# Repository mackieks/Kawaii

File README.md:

<picture> <source media="(prefers-color-scheme: dark)" srcset="images/kawaii_logo_white.png">  </picture> 

Kawaii is a functional metal Nintendo Wii keychain created by YveltalGriffin, Wesk and Ding.

It's a technical tour de force that prioritizes aesthetics over practicality, and **fully** utilizes the OMEGA trim.

Kawaii may be the zenith of Wii portablizing as an artform.

## Features:
- [x] 60 x 60 x 15.8mm CNC aluminum chassis
- [x] Anodized, with laser-etched artwork
- [x] Fake compliance markings
- [x] Keychain / tassel loop
- [x] OMEGA-trimmed undervolted Hollywood-2 Wii Mini motherboard
- [x] [AVEflex](https://github.com/mackieks/AVEflex) and [nandFlex](https://github.com/mackieks/nandFlex)
- [x] Powered by [Thundervolt](https://github.com/mackieks/thundervolt)
- [x] Internal microSD card for homebrew and games
- [x] Six internal addressable RGB LEDs
- [x] Magnetic pogo pin docking connector
- [x] Composite video, 480p YPbPr, and stereo audio output
- [x] 4-player GameCube controller connectivity via magnetic dock

## Gallery

## Building One

Kawaii is 100% open source, but due to the extremely challenging nature of the build, no assembly guide or build tutorial is provided. Keep in mind that this project is **portablizer jewelry** (it's literally a keychain) and **NOT** a console you want to daily drive.

Check out [the hardware folder](https://github.com/mackieks/Kawaii/tree/main/hardware) for all of the MCAD, ECAD, and BOM files. A full MCAD assembly is provided in both F3D and STEP format, which shows how everything fits together. The [BitBuilt thread](https://bitbuilt.net/forums/index.php?threads/kawaii.6474/) has lots of pictures from the assembly process of two Kawaiis and is a valuable resource. 

## World's Smallest?

Whether the Kawaii is the world's smallest functioning Wii is up for debate. Since it requires a dock or bundle of adapter cables to play games on a TV, it's certainly not the world's smallest _fully self-contained_ Wii— that's still loopj's [Short Stack](https://github.com/loopj/short-stack). Kawaii also requires an external fan to stay cool enough to touch during extended use.

Still, the Kawaii does contain a complete Wii. Its only inputs are power and GameCube controllers, and its only outputs are analog audio and video. So it may be the smallest functional Wii build, but not the smallest functional Wii console. The distinction is semantic and largely irrelevant to the project's goal, which was to create something beautiful, not to claim a title. 😄

## Credits

- YveltalGriffin: Concept, ECAD, MCAD, artwork, assembly
- Wesk: MCAD, sexy renders
- Ding: CNC machining, anodization, laser etching

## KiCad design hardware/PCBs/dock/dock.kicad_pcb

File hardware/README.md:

# Hardware

The top-level MCAD assemblies in F3D and STEP format are the main reference for the overall build. STLs for the 3D-printed components are provided for convenience.

## PCB Ordering Specs:

- Dock: 1mm, ENIG recommended, electropolished stencil, [Mouser Cart](https://www.mouser.com/Tools/Project/Share?AccessID=a96e376ba1)
- kawaiiSD: 0.6mm, electropolished stencil and jig, [Mouser Cart](https://www.mouser.com/Tools/Project/Share?AccessID=177a5d7398)
- riser: 0.8mm
- rgb: 0.6mm, electropolished stencil

## List of Kawaii components:
- [x] CNC machined, anodized, and laser-etched aluminum shell (two pieces)
- [x] Hollywood-2 Wii Mini OMEGA trim, [AVEflex](https://github.com/mackieks/AVEflex), [nandFlex](https://github.com/mackieks/nandFlex), and [Thundervolt](https://github.com/mackieks/thundervolt)
- [x] Internal kawaiiSD PCB
- [x] Pogo pin riser PCB
- [x] RGB LED PCB
- [x] MHF4 female pigtails [link](https://www.aliexpress.us/item/3256802754472981.html)
- [x] 3D-printed lightpipes (x2)
- [x] 12-pin magnetic pogo pin connector [link 1](https://www.aliexpress.us/item/3256804525551011.html), [link 2](https://www.aliexpress.us/item/3256807252344568.html)
- [x] Various fasteners (see MCAD)

## List of dock components:
- [x] 3D-printed dock (three pieces)
- [x] Dock PCB (including four trimmed/cleaned-up Wii GCC ports)
- [x] LED lightpipe (PLPC2-100)
- [x] Various fasteners (see MCAD)

## Miscellaneous assembly/usage notes:
- [x] A heavily-undervolted Hollywood-2 Wii Mini is mandatory. A Hollywood-1, or any variant at stock voltages, will run way too hot
- [x] Unless you live in Alaska or Siberia, the unit will need an external source of airflow (fan, AC, open window, etc.) to stay cool enough to touch during operation
- [x] Use 0.5mm foam tape to secure the RGB LED PCB to the Kawaii shell
- [x] Use a file to post-process the Wii GCC ports. They have to be really uniform and square to fit into the shell properly (see thread)
- [x] Use a camcorder pinout 3.5mm-to-RCA cable for A/V. Check the schematic for pinout details. [link](https://www.amazon.com/dp/B08V1SV8BL)
- [x] Use a Samsung / LG pinout 3.5mm-to-component cable for YPbPR. Check the schematic for pinout details. [link](https://www.amazon.com/dp/B09ZJTZ5NL)

## License

Solderpad Hardware License v2.1

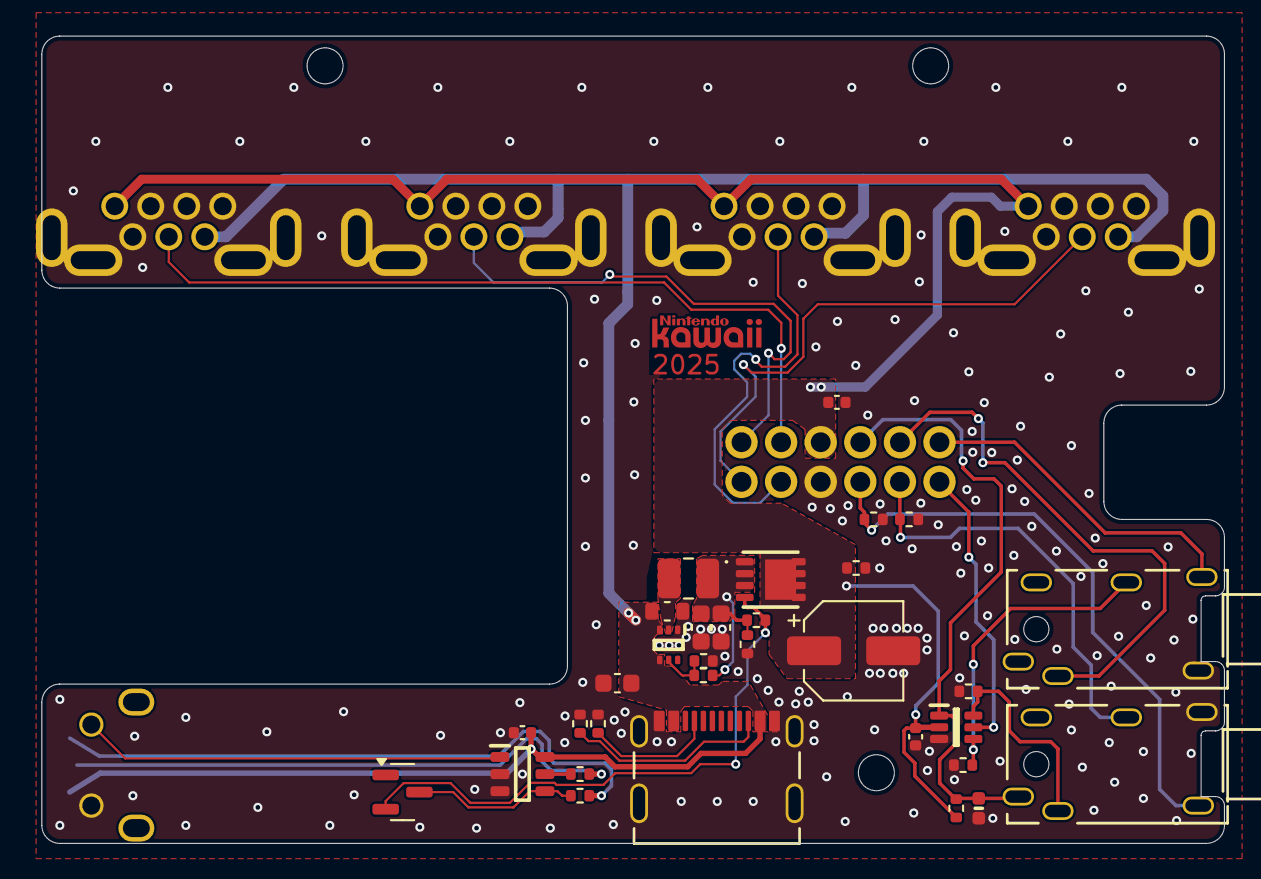
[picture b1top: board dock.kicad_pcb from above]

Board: 2 copper layers, 65.7 x 44.8 mm, 39 parts (1 on the bottom side), 26 nets.

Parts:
C1, C3, C4, C5: 22μF; C_0603_1608Metric
C2, C8: 0.1μF; C_0402_1005Metric
C6: 68uF; CP_Elec_5x5.8
C7: 1uF; C_0402_1005Metric
D1: BAT54C; SOT-23
D2: LED_Dual_KAK; 155124RG73200
D3: GG0402052R542P; DIONC1006X55N
IC1: MAX16054AZT+T; SOT95P275X110-6N
IC2: TPS62A06ADRLR; SOTFL50P160X60-6N
IC3: TS5A4624DCKR; SOT65P210X110-6N
J1: 217179-0001; 2171790001
J2: https://www.aliexpress.us/item/3256804525568376.h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; pogo
J3, J4: 54-00176; 54-00176_TEN
J5, J6, J7, J8: Wii GCC Port; gcc
L1: MGV252010R22M-10; L_1008_2520Metric
Q2: SI7111EDN-T1-GE3; SQS401ENT1_BE3
R2, R3, R8, R10, R11: 5.1k; R_0402_1005Metric
R4, R5: 1k; R_0402_1005Metric
R6: 453k; R_0402_1005Metric
R7, R9: 100k; R_0402_1005Metric
R12, R13, R14, R15: 75; R_0402_1005Metric
SW1: FSMRA4JH04; 6x6x8mm_tact_ra

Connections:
/LED_G: D2.3 (K2), R5.1
/LED_R: D2.1 (K1), R4.1
AUDIO_L: J2.5, J4.4
AUDIO_R: J2.6, J4.1
CVBS: IC3.4 (NC), J4.3, R14.1
GND: C1.2, C2.2, C3.2, C4.2, C5.2, C6.2, C7.2, C8.2, D3.1 (A1), IC1.2 (GND), IC1.3 (CLEAR), IC2.1 (GND), IC3.3 (GND), J1.13 (GND), J1.14 (GND), J1.15 (GND), J1.16 (GND), J1.A1/B12 (GND_2), J1.B1/A12 (GND), J2.10, J3.1, J4.2, J5.2, J5.3, J5.4, J5.5, J5.8, J5.9, J6.2, J6.3, J6.4, J6.5, J6.8, J6.9, J7.2, J7.3, J7.4, J7.5, J7.8, J7.9, J8.2, J8.3, J8.4, J8.5, J8.8, J8.9, R2.2, R3.2, R7.2, R8.2, R10.2, R12.2, R13.2, R14.2, R15.2, SW1.1 (A)
Mode: D3.2 (A2), IC3.1 (IN), J2.4, J3.5, R11.2
unnamed: IC1.1 (IN), SW1.2 (B)
unnamed: IC2.5 (FB), R6.2, R7.1
unnamed: IC2.2 (SW), L1.1
unnamed: J1.A5 (CC1), R3.1
unnamed: J1.B5 (CC2), R2.1
P1: J2.12, J8.6
P2: J2.11, J7.6
P3: J2.1, J6.6
P4: J2.2, J5.6
Pb: J2.8, J3.3, R15.1
Pr: J2.9, J3.2, R12.1
VBUS: C1.1, C2.1, C3.1, D2.2 (A), IC1.6 (VCC), IC2.3 (VIN), IC2.4 (EN), J1.A4/B9 (VBUS), J1.B4/A9 (VBUS), J5.7, J6.7, J7.7, J8.7
VBUS_EN: D1.3, IC1.4 (~OUT), R5.2
VKAWAII: C4.1, C5.1, L1.2, Q2.1 (S), Q2.2 (S), Q2.3 (S), R6.1, R8.1, R9.1
VKAWAII_EN: D1.2, Q2.4 (G), R9.2
VKAWAII_SWITCHED: C6.1, C7.1, C8.1, IC3.2 (V+), J2.3, J5.1, J6.1, J7.1, J8.1, Q2.5 (D), Q2.6 (D), Q2.7 (D), Q2.8 (D), Q2.9 (D), R10.1, R11.1
Y: IC3.6 (NO), J3.4, R13.1
Y/CVBS: IC3.5 (COM), J2.7
~VBUS_EN: IC1.5 (OUT), R4.2

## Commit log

2025-07-09 Add everything!
2025-07-09 remove random files
2025-07-10 Reorganize CAD, add technical drawings
